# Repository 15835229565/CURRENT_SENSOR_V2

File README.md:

CURRENT_SENSOR_V2
=================

HW and SW for current sensor

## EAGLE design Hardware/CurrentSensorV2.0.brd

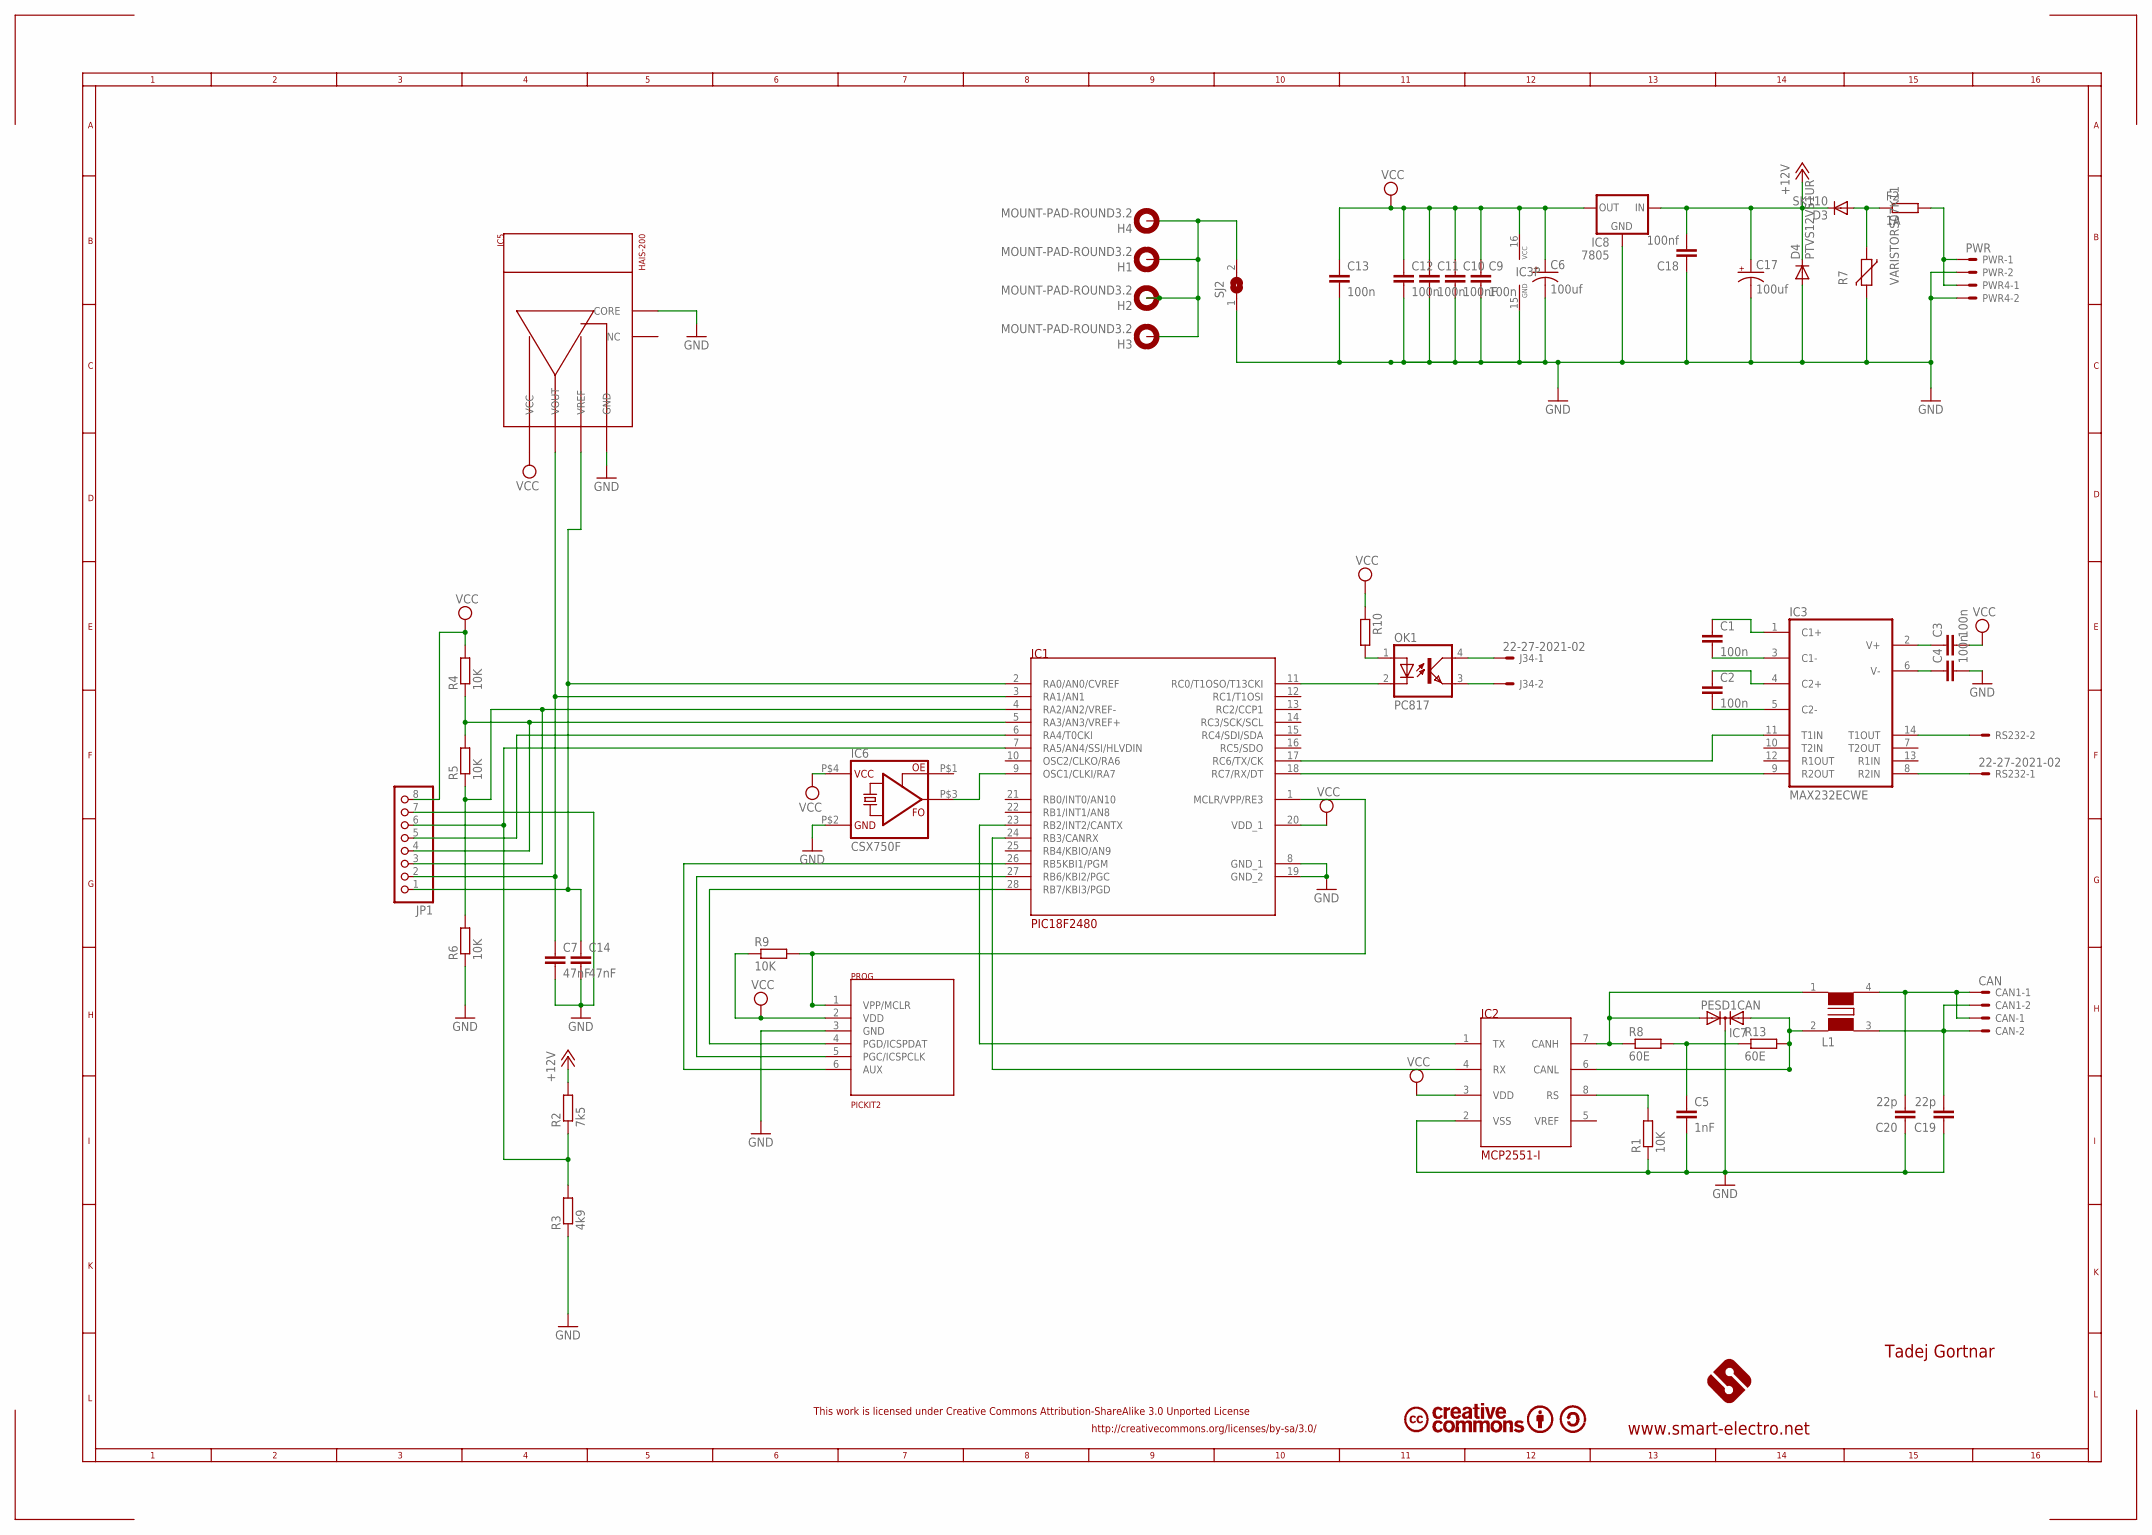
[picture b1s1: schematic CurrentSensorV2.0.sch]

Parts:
C1, C2, C3, C4, C9, C11, C12, C13: 100n; C0805K
C5: 1nF; C0805
C6, C17: 100uf; PANASONIC_C
C7, C14: 47nF; C0805K
C10: 100nF; C0805K
C18: 100nf; C0805
C19, C20: 22p; C0805
CAN, CAN1: CAN; 6410-02
D3: SK110; MINIMELF
D4: PTVS12VS1UR; SOD323-W
F2: 1A; R1206
H1, H2, H3, H4: MOUNT-PAD-ROUND3.2; 3,2-PAD
IC1: PIC18F2480; SO-28W
IC2: MCP2551-I; SO-08
IC3: MAX232ECWE; SO16L
IC5: HAIS-200; HAIS-P
IC6: CSX750F; CSX750
IC7: PESD1CAN; SOT23
IC8: 7805; SOT223
J34: 22-27-2021-02; 6410-02
JP1: PINHD-1X8; 1X08
L1: WE-DD_M/S
OK1: PC817; DIL04
PROG: PICKIT2; PINHD-1X6
PWR, PWR4: PWR; 6410-02
R1, R4, R5, R6, R9: 10K; M0805
R2: 7k5; M0805
R3: 4k9; M0805
R7: VARISTORS07K11; S07K11
R8, R13: 60E; R0805
R10: R-EU_M0805; M0805
RS232: 22-27-2021-02; 6410-02
SJ2: SJ

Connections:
+12V: C17.+, C18.2, D3.C, D4.C, IC8.1 (IN), R2.2
AGND: H1.B3,2, H2.B3,2, H3.B3,2, H4.B3,2, SJ2.2
GND: C4.2, C5.2, C6.-, C7.2, C9.2, C10.2, C11.2, C12.2, C13.2, C14.2, C17.-, C18.1, C19.1, C20.1, D4.A, IC1.8 (GND_1), IC1.19 (GND_2), IC2.2 (VSS), IC3.15 (GND), IC5.P$2 (GND), IC5.P$5 (CORE), IC6.P$2 (GND), IC7.3 (C), IC8.2 (GND), JP1.7, PROG.3 (GND), PWR.2, PWR4.2, R1.1, R3.1, R6.1, R7.2, SJ2.1
unnamed: IC1.1 (MCLR/VPP/RE3), PROG.1 (VPP/MCLR), R9.2
unnamed: IC1.24 (RB3/CANRX), IC2.4 (RX)
unnamed: IC2.7 (CANH), IC7.1 (A1), L1.1 (2), R8.1
unnamed: IC1.23 (RB2/INT2/CANTX), IC2.1 (TX)
unnamed: C7.1, IC1.3 (RA1/AN1), IC5.P$3 (VOUT), JP1.2
unnamed: C14.1, IC1.2 (RA0/AN0/CVREF), IC5.P$4 (VREF), JP1.1
unnamed: IC1.9 (OSC1/CLKI/RA7), IC6.P$3 (FO)
unnamed: IC1.28 (RB7/KBI3/PGD), PROG.4 (PGD/ICSPDAT)
unnamed: IC1.27 (RB6/KBI2/PGC), PROG.5 (PGC/ICSPCLK)
unnamed: IC1.26 (RB5KBI1/PGM), PROG.6 (AUX)
unnamed: IC1.17 (RC6/TX/CK), IC3.11 (T1IN)
unnamed: IC1.18 (RC7/RX/DT), IC3.9 (R2OUT)
unnamed: IC3.8 (R2IN), RS232.1
unnamed: IC3.14 (T1OUT), RS232.2
unnamed: C3.1, IC3.2 (V+)
unnamed: C4.1, IC3.6 (V-)
unnamed: C1.1, IC3.1 (C1+)
unnamed: C1.2, IC3.3 (C1-)
unnamed: IC1.11 (RC0/T1OSO/T13CKI), OK1.2 (C)
unnamed: C5.1, R8.2, R13.1
unnamed: C2.1, IC3.4 (C2+)
unnamed: C2.2, IC3.5 (C2-)
unnamed: IC1.4 (RA2/AN2/VREF-), JP1.3, R5.1, R6.2
unnamed: IC1.5 (RA3/AN3/VREF+), JP1.4, R4.1, R5.2
unnamed: IC1.6 (RA4/T0CKI), JP1.5
unnamed: IC1.7 (RA5/AN4/SSI/HLVDIN), JP1.6, R2.1, R3.2
unnamed: OK1.1 (A), R10.2
unnamed: J34.2, OK1.3 (EMIT)
unnamed: J34.1, OK1.4 (COL)
unnamed: IC2.8 (RS), R1.2
unnamed: IC2.6 (CANL), IC7.2 (A2), L1.2 (1), R13.2
unnamed: F2.2, PWR.1, PWR4.1
unnamed: D3.A, F2.1, R7.1
unnamed: C20.2, CAN.1, CAN1.1, L1.4 (3)
unnamed: C19.2, CAN.2, CAN1.2, L1.3 (4)
VCC: C3.2, C6.+, C9.1, C10.1, C11.1, C12.1, C13.1, IC1.20 (VDD_1), IC2.3 (VDD), IC3.16 (VCC), IC5.P$1 (VCC), IC6.P$4 (VCC), IC8.3 (OUT), JP1.8, PROG.2 (VDD), R4.2, R9.1, R10.1

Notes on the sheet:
Tadej Gortnar
http://creativecommons.org/licenses/by-sa/3.0/
This work is licensed under Creative Commons Attribution-ShareAlike 3.0 Unported License
www.smart-electro.net

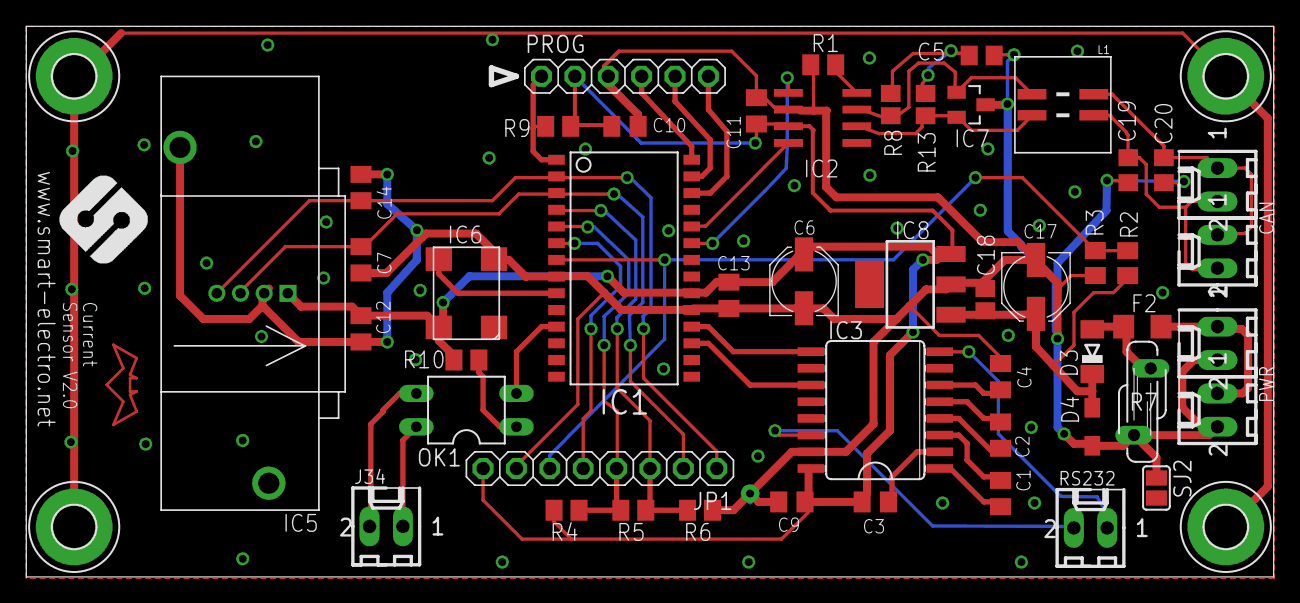
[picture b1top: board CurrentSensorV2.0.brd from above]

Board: 2 copper layers, 94.9 x 41.9 mm, 53 parts (0 on the bottom side), 39 nets.
